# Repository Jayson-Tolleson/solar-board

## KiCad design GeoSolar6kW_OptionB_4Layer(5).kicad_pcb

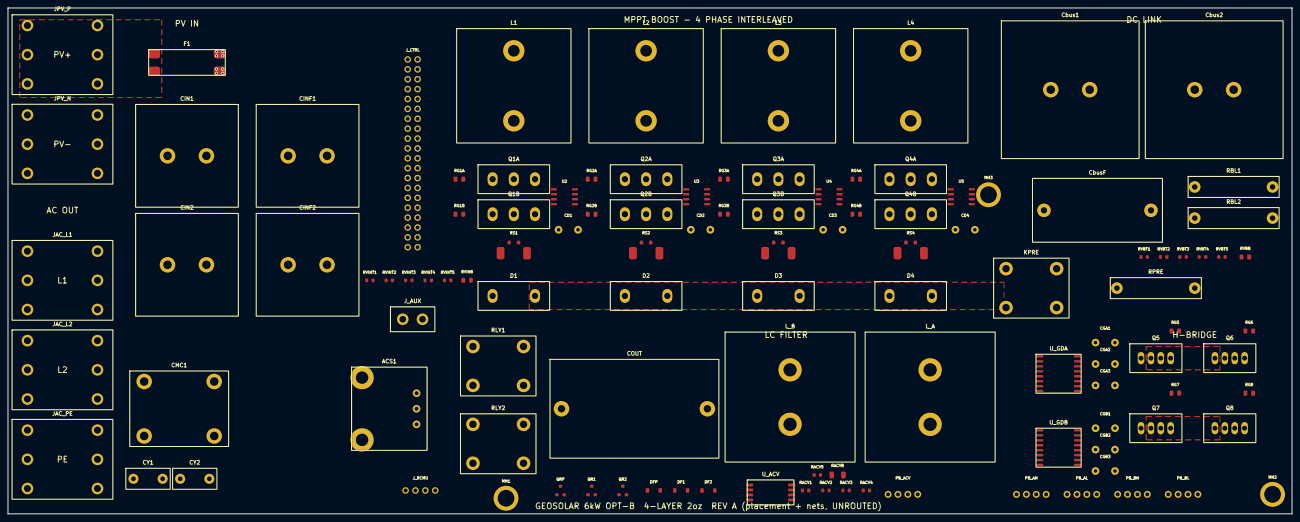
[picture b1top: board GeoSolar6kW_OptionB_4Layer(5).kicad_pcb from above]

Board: 4 copper layers, 330.0 x 130.0 mm, 114 parts (0 on the bottom side), 100 nets, no tracks yet.

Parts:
ACS1: Hall current sensor +/-50A; ACS_MOD
CD1, CD2, CD3, CD4: 1uF 500V; CAP_LEAD_P5
CGA1, CGA2, CGA3: 1uF 500V; CAP_LEAD_P5
CGB1, CGB2, CGB3: 1uF 500V; CAP_LEAD_P5
CIN1, CIN2: 220uF 500V electrolytic snap-in D25; CAP_SNAP_D25
CINF1, CINF2: LCSC C240420 220uF 500V horn D25xL45; CAP_SNAP_D25
CMC1: Common-mode choke; CMC_4P
COUT: 3uF X2 275VAC; CAP_X2_P37.5
CY1: Y cap L1-PE; CAP_Y_P7.5
CY2: Y cap L2-PE; CAP_Y_P7.5
Cbus1, Cbus2: 1000uF 500V; CAP_SNAP_D36
CbusF: 2.2uF 630V film; CAP_BOX_P27.5
D1, D2, D3, D4: 650V SiC; TO247_2
DF1, DF2: Flyback diode; SOD123
DFP: Flyback diode; SOD123
F1: XFCN XF-508PVS-A-B-R fuse clip; FUSE_CLIP_SMD4
JAC_L1, JAC_L2: Terminal LCSC C45384762; TERM_DIP6_26x20.6
JAC_PE: Terminal LCSC C45384762; TERM_DIP6_26x20.6
JPV_N: Terminal LCSC C45384762; TERM_DIP6_26x20.6
JPV_P: Terminal LCSC C45384762; TERM_DIP6_26x20.6
J_AUX: AUX +12V in; TERM_2P_5.08
J_CTRL: Controller I/F (F280049C card / bench); HDR_2x20
J_RCMU: RCMU interface; HDR_1x4
KPRE: Precharge bypass relay; RELAY_4P
L1, L2, L3, L4: ~470uH Isat>=18.3A; IND_BOOST
L_A: ~76uH Isat>46A; IND_FILT
L_B: ~76uH Isat>46A; IND_FILT
MH1, MH2, MH3: M4 hole; MH_M4
PB_ACV: Isolated bias for ACV amp; PSU_SIP4
PB_AH: Isolated bias 12V->15V; PSU_SIP4
PB_AL: Isolated bias 12V->15V; PSU_SIP4
PB_BH: Isolated bias 12V->15V; PSU_SIP4
PB_BL: Isolated bias 12V->15V; PSU_SIP4
Q1A, Q2A, Q3A, Q4A: 650V SiC; TO247_3
Q1B, Q2B, Q3B, Q4B: 650V SiC (DNP opt.); TO247_3
Q5, Q6, Q7, Q8: 650V SiC TO-247-4 (D,S,KS,G - verify); TO247_4
QR1, QR2: Relay driver NMOS; SOT23
QRP: Relay driver NMOS; SOT23
RACV1, RACV2, RACV3, RACV4, RACV5: 330k; R0603
RACVB: 1k; R1206
RBL1, RBL2: Bleeder 100k; R_AXIAL_P20
RG1A, RG1B, RG2A, RG2B, RG3A, RG3B, RG4A, RG4B, RG5, RG6, RG7, RG8: 10R; R0805
RLY1: AC relay L1 40A; RELAY_4P
RLY2: AC relay L2 40A; RELAY_4P
RPRE: Precharge R; R_AXIAL_P20
RS1, RS2, RS3, RS4: 3mR Kelvin; SHUNT_4T
RVBB: 10k; R0805
RVBT1, RVBT2, RVBT3, RVBT4, RVBT5: 330k; R0603
RVINB: 10k; R0805
RVINT1, RVINT2, RVINT3, RVINT4, RVINT5: 330k; R0603
U2, U3, U4, U5: UCC27524A; SOIC8
U_ACV: Isolated amp (AMC1301-class, VERIFY PINMAP); SOIC8W
U_GDA: Isolated dual driver (UCC21520-class, VERIFY PINM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; SOIC16W
U_GDB: Isolated dual driver (UCC21520-class, VERIFY PINM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; SOIC16W

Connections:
+3V3: J_CTRL.1, U_ACV.5
+5V: ACS1.3, CGA3.1, CGB3.1, J_CTRL.2, J_RCMU.1, U_GDA.2, U_GDA.13, U_GDB.2, U_GDB.13
+12V: CD1.1, CD2.1, CD3.1, CD4.1, DF1.1, DF2.1, DFP.1, J_AUX.1, KPRE.3, PB_ACV.1, PB_AH.1, PB_AL.1, PB_BH.1, PB_BL.1, RLY1.3, RLY2.3, U2.6, U3.6, U4.6, U5.6
ACI_SENSE: ACS1.5, J_CTRL.27
ACS_OUT_A: ACS1.2, CMC1.1
ACV_M1: RACV1.2, RACV2.1
ACV_M2: RACV2.2, RACV3.1
ACV_M3: RACV3.2, RACV4.1
ACV_M4: RACV4.2, RACV5.1
ACV_N: RACV5.2, RACVB.1, U_ACV.8
ACV_OUTN: J_CTRL.26, U_ACV.6
ACV_OUTP: J_CTRL.25, U_ACV.4
ACV_VDD1: PB_ACV.3, U_ACV.1
AC_L1: CMC1.3, CY1.1, JAC_L1.1, JAC_L1.2, JAC_L1.3, JAC_L1.4, JAC_L1.5, JAC_L1.6, RACV1.1
AC_L2: CMC1.4, CY2.1, JAC_L2.1, JAC_L2.2, JAC_L2.3, JAC_L2.4, JAC_L2.5, JAC_L2.6, PB_ACV.4, RACVB.2, U_ACV.2, U_ACV.7
A_HI_DRV: RG5.1, U_GDA.8
A_HI_VDD: CGA1.1, PB_AH.3, U_GDA.9
A_LO_DRV: RG6.1, U_GDA.12
A_LO_VDD: CGA2.1, PB_AL.3, U_GDA.5
BLD_MID: RBL1.2, RBL2.1
B_HI_DRV: RG7.1, U_GDB.8
B_HI_VDD: CGB1.1, PB_BH.3, U_GDB.9
B_LO_DRV: RG8.1, U_GDB.12
B_LO_VDD: CGB2.1, PB_BL.3, U_GDB.5
DRV_1A: RG1A.1, U2.4
DRV_1B: RG1B.1, U2.3
DRV_2A: RG2A.1, U3.4
DRV_2B: RG2B.1, U3.3
DRV_3A: RG3A.1, U4.4
DRV_3B: RG3B.1, U4.3
DRV_4A: RG4A.1, U5.4
DRV_4B: RG4B.1, U5.3
DRV_EN: J_CTRL.9, U2.1, U2.5, U3.1, U3.5, U4.1, U4.5, U5.1, U5.5
FILT_A: COUT.1, L_A.2, RLY1.1
FILT_B: COUT.2, L_B.2, RLY2.1
GATE_1A: Q1A.1, RG1A.2
GATE_1B: Q1B.1, RG1B.2
GATE_2A: Q2A.1, RG2A.2
GATE_2B: Q2B.1, RG2B.2
GATE_3A: Q3A.1, RG3A.2
GATE_3B: Q3B.1, RG3B.2
GATE_4A: Q4A.1, RG4A.2
GATE_4B: Q4B.1, RG4B.2
GND: ACS1.4, CD1.2, CD2.2, CD3.2, CD4.2, CGA2.2, CGA3.2, CGB2.2, CGB3.2, CIN1.2, CIN2.2, CINF1.2, CINF2.2, Cbus1.2, Cbus2.2, CbusF.2, JPV_N.1, JPV_N.2, JPV_N.3, JPV_N.4, JPV_N.5, JPV_N.6, J_AUX.2, J_CTRL.3, J_CTRL.4, J_CTRL.33, J_CTRL.34, J_RCMU.2, PB_ACV.2, PB_AH.2, PB_AL.2, PB_AL.4, PB_BH.2, PB_BL.2, PB_BL.4, Q6.2, Q6.3, Q8.2, Q8.3, QR1.2, QR2.2, QRP.2, RBL2.2, RS1.2, RS2.2, RS3.2, RS4.2, RVBB.2, RVINB.2, U2.2, U3.2, U4.2, U5.2, U_ACV.3, U_GDA.6, U_GDA.15, U_GDB.6, U_GDB.15
HB_A_HI_G: Q5.4, RG5.2
HB_A_HI_PWM: J_CTRL.11, U_GDA.1
HB_A_LO_G: Q6.4, RG6.2
HB_A_LO_PWM: J_CTRL.12, U_GDA.16
HB_B_HI_G: Q7.4, RG7.2
HB_B_HI_PWM: J_CTRL.13, U_GDB.1
HB_B_LO_G: Q8.4, RG8.2
HB_B_LO_PWM: J_CTRL.14, U_GDB.16
HB_DIS: J_CTRL.10, U_GDA.3, U_GDB.3
HVBUS: Cbus1.1, Cbus2.1, CbusF.1, KPRE.2, Q5.1, Q7.1, RBL1.1, RPRE.2, RVBT1.1
HV_RAW: D1.2, D2.2, D3.2, D4.2, KPRE.1, RPRE.1
IS_1_N: J_CTRL.16, RS1.4
IS_1_P: J_CTRL.15, RS1.3
IS_2_N: J_CTRL.18, RS2.4
IS_2_P: J_CTRL.17, RS2.3
IS_3_N: J_CTRL.20, RS3.4
IS_3_P: J_CTRL.19, RS3.3
IS_4_N: J_CTRL.22, RS4.4
IS_4_P: J_CTRL.21, RS4.3
LEG_A: CGA1.2, L_A.1, PB_AH.4, Q5.2, Q5.3, Q6.1, U_GDA.10
LEG_B: CGB1.2, L_B.1, PB_BH.4, Q7.2, Q7.3, Q8.1, U_GDB.10
PE: CY1.2, CY2.2, JAC_PE.1, JAC_PE.2, JAC_PE.3, JAC_PE.4, JAC_PE.5, JAC_PE.6
PV_P: F1.1, F1.2, JPV_P.1, JPV_P.2, JPV_P.3, JPV_P.4, JPV_P.5, JPV_P.6
PWM_1: J_CTRL.5, U2.7, U2.8
PWM_2: J_CTRL.6, U3.7, U3.8
PWM_3: J_CTRL.7, U4.7, U4.8
PWM_4: J_CTRL.8, U5.7, U5.8
RCMU_SIG: J_CTRL.31, J_RCMU.3
RCMU_TRIP: J_CTRL.32, J_RCMU.4
RLY_L1_DRV: J_CTRL.29, QR1.1
RLY_L1_N: DF1.2, QR1.3, RLY1.4
RLY_L2_DRV: J_CTRL.30, QR2.1
RLY_L2_N: DF2.2, QR2.3, RLY2.4
RLY_OUT_A: ACS1.1, RLY1.2
RLY_OUT_B: CMC1.2, RLY2.2
RLY_PRE_DRV: J_CTRL.28, QRP.1
RLY_PRE_N: DFP.2, KPRE.4, QRP.3
SRC_1: Q1A.3, Q1B.3, RS1.1
SRC_2: Q2A.3, Q2B.3, RS2.1
SRC_3: Q3A.3, Q3B.3, RS3.1
SRC_4: Q4A.3, Q4B.3, RS4.1
SW1: D1.1, L1.2, Q1A.2, Q1B.2
SW2: D2.1, L2.2, Q2A.2, Q2B.2
SW3: D3.1, L3.2, Q3A.2, Q3B.2
SW4: D4.1, L4.2, Q4A.2, Q4B.2
VBUS_SENSE: J_CTRL.24, RVBB.1, RVBT5.2
VB_N1: RVBT1.2, RVBT2.1
VB_N2: RVBT2.2, RVBT3.1
VB_N3: RVBT3.2, RVBT4.1
VB_N4: RVBT4.2, RVBT5.1
VIN: CIN1.1, CIN2.1, CINF1.1, CINF2.1, F1.3, F1.4, L1.1, L2.1, L3.1, L4.1, RVINT1.1
VIN_N1: RVINT1.2, RVINT2.1
VIN_N2: RVINT2.2, RVINT3.1
VIN_N3: RVINT3.2, RVINT4.1
VIN_N4: RVINT4.2, RVINT5.1
VIN_SENSE: J_CTRL.23, RVINB.1, RVINT5.2
